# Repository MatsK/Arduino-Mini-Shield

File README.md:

# Arduino Mini Shield

## Concept

If you don't need a full size "Arduino Shield" I have made a Mini shield that just have D8 - D13 and Power +5v, +3,3v and GND on the other side

## Shields

### ArduinoMiniShield_Blank.sch/.brd

A blank template.

### HC-06_Arduino_UNO_Adapter.sch/.brd

Bluetooth HC06 shield. Note! Untested. Boards ordered from OSHpark ETA 2016-02-23

## Pictures

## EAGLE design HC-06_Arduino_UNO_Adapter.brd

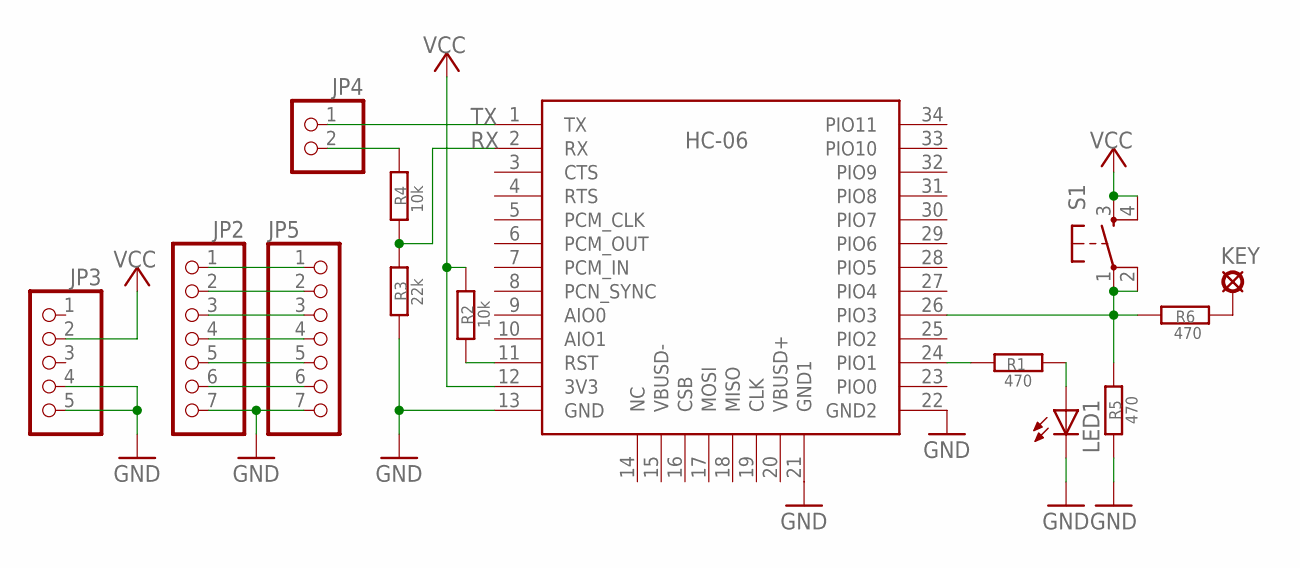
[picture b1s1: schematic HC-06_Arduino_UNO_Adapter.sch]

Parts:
HC-06: HC_05; BLUETOOTH_SMD
JP2, JP5: PINHD-1X7; 1X07
JP3: PINHD-1X5; 1X05
JP4: PINHD-1X2; 1X02
KEY: LSP10
LED1: LED3MM
R1, R5, R6: 470; 0204/5
R2, R4: 10k; 0204/5
R3: 22k; 0204/5
S1: TACTILE-SWITCH-PTH; TAC-SWITCH-PTH

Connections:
GND: HC-06.13 (GND), HC-06.21 (GND1), HC-06.22 (GND2), JP2.7, JP3.4, JP3.5, JP5.7, LED1.K (C), R3.1, R5.2
KEY: KEY.MP, R6.1
unnamed: LED1.A, R1.2
unnamed: HC-06.24 (PIO1), R1.1
unnamed: HC-06.11 (RST), R2.2
unnamed: JP2.1, JP5.1
unnamed: JP2.2, JP5.2
unnamed: JP2.3, JP5.3
unnamed: JP2.4, JP5.4
unnamed: HC-06.26 (PIO3), R5.1, R6.2, S1.1, S1.2
unnamed: JP4.2, R4.2
unnamed: JP2.5, JP5.5
unnamed: JP2.6, JP5.6
RX: HC-06.2 (RX), R3.2, R4.1
TX: HC-06.1 (TX), JP4.1
VCC: HC-06.12 (3V3), JP3.2, R2.1, S1.3, S1.4

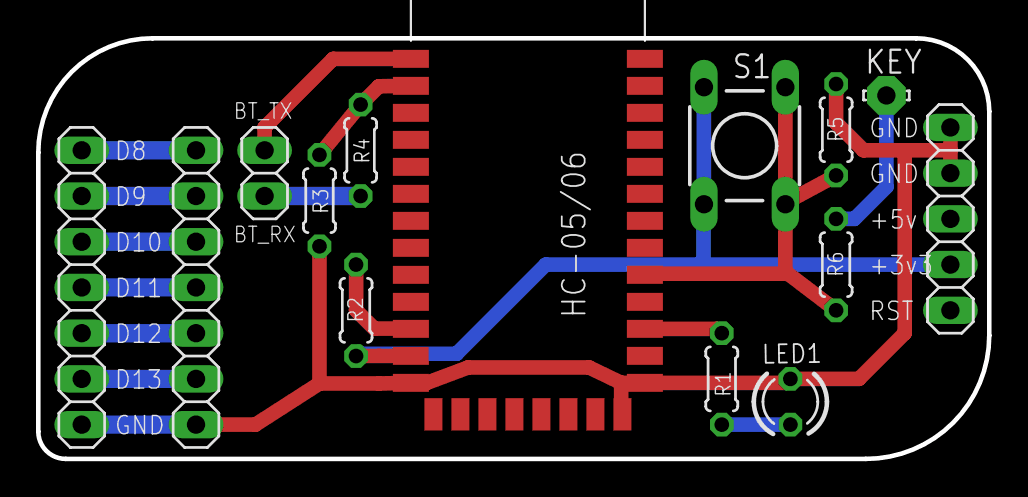
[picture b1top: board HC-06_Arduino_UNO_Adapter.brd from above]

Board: 2 copper layers, 52.8 x 23.4 mm, 14 parts (0 on the bottom side), 16 nets.

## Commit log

2016-02-08 :space_invader: Added .gitattributes & .gitignore files
2016-02-08 First version
2016-02-08 Screen shoots and added README
2016-02-08 Url miss
2016-02-09 Added shield for Bluetooth module HC06
2016-02-09 minor changes

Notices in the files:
parts and their libraries:
GeekAmmo: Licensing:Creative Commons ShareAlike 4.0 International - https://creativecommons.org/licenses/by-sa/4.0
